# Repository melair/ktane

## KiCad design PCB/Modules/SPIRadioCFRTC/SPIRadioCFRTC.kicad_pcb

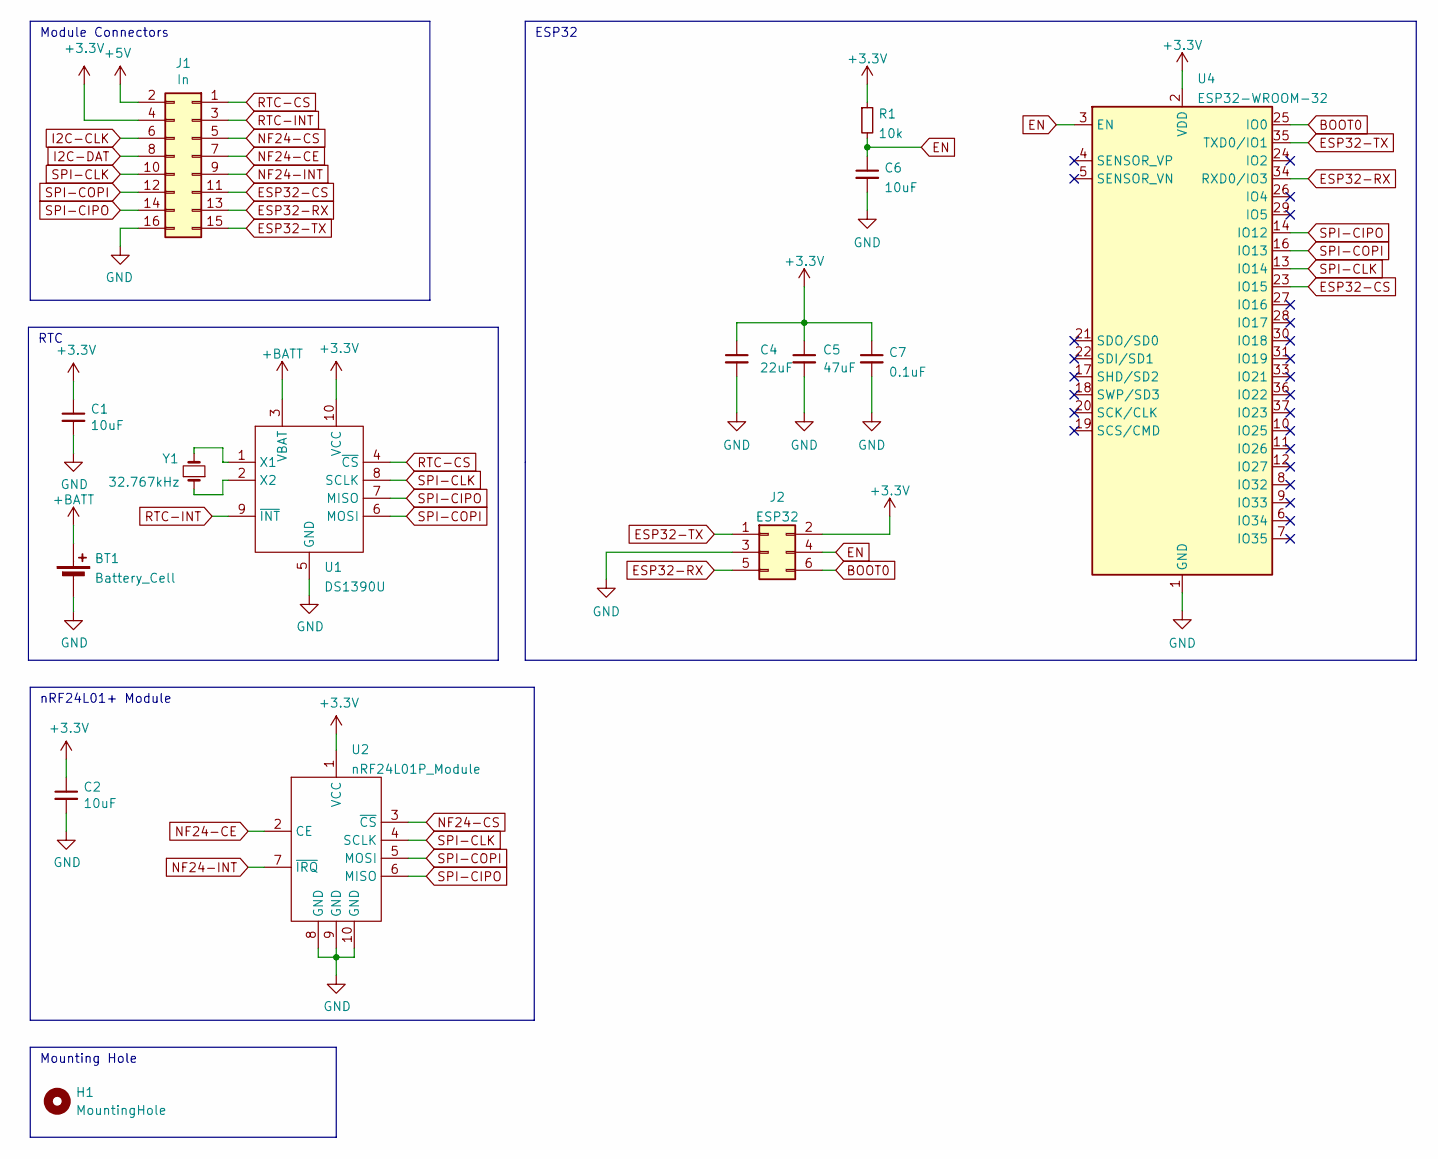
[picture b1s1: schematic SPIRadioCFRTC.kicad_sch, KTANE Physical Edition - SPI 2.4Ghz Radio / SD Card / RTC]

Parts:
BT1: Battery_Cell; CellHolder
C1, C2, C6: 10uF; C_0603_1608Metric
C4: 22uF; C_0603_1608Metric
C5: 47uF; C_0603_1608Metric
C7: 0.1uF; C_0603_1608Metric
H1: MountingHole; MountingHole_3.2mm_M3
J1: In; PinHeader_2x08_P2.54mm_Vertical-Centered
J2: ESP32; Tag-Connect_TC2030-IDC-NL_2x03_P1.27mm_Vertical
R1: 10k; R_0603_1608Metric
U1: DS1390U; MSOP-10_3x3mm_P0.5mm
U2: nRF24L01P_Module; NRF24L01P-Module
U4: ESP32-WROOM-32; ESP32-WROOM-32U
Y1: 32.767kHz; Crystal_SMD_3215-2Pin_3.2x1.5mm

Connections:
+3.3V: C1.1, C2.1, C4.1, C5.1, C7.1, J1.4, J2.2, R1.1, U1.10 (VCC), U2.1 (VCC), U4.2 (VDD)
+5V: J1.2
+BATT: BT1.1 (+), U1.3 (VBAT)
BOOT0: J2.6, U4.25 (IO0)
EN: C6.1, J2.4, R1.2, U4.3 (EN)
ESP32-CS: J1.11, U4.23 (IO15)
ESP32-RX: J1.13, J2.5, U4.34 (RXD0/IO3)
ESP32-TX: J1.15, J2.1, U4.35 (TXD0/IO1)
GND: BT1.2 (-), C1.2, C2.2, C4.2, C5.2, C6.2, C7.2, J1.16, J2.3, U1.5 (GND), U2.8 (GND), U2.9 (GND), U2.10 (GND), U4.1 (GND), U4.15 (GND), U4.38 (GND), U4.39 (GND)
I2C-CLK: J1.6
I2C-DAT: J1.8
NF24-CE: J1.7, U2.2 (CE)
NF24-CS: J1.5, U2.3 (~CS)
NF24-INT: J1.9, U2.7 (~IRQ)
unnamed: U1.1 (X1), Y1.2
unnamed: U1.2 (X2), Y1.1
RTC-CS: J1.1, U1.4 (~CS)
RTC-INT: J1.3, U1.9 (~INT)
SPI-CIPO: J1.14, U1.7 (MISO), U2.6 (MISO), U4.14 (IO12)
SPI-CLK: J1.10, U1.8 (SCLK), U2.4 (SCLK), U4.13 (IO14)
SPI-COPI: J1.12, U1.6 (MOSI), U2.5 (MOSI), U4.16 (IO13)

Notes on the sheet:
RTC
Module Connectors
nRF24L01+ Module
Mounting Hole
ESP32

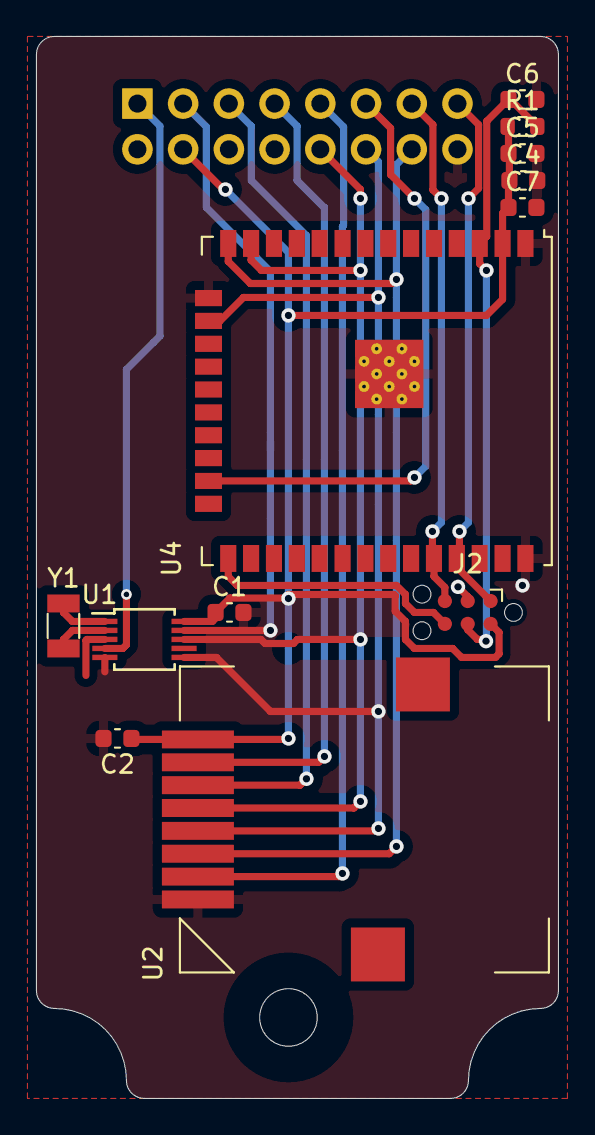
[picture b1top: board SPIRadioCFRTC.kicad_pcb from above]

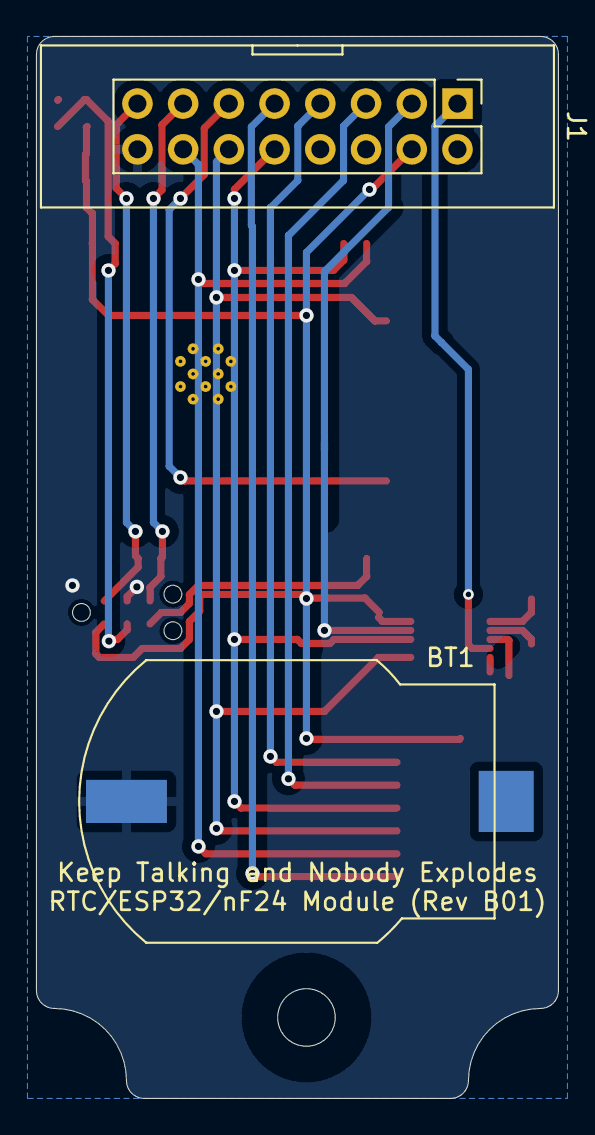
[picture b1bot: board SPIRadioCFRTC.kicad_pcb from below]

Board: 2 copper layers, 29.0 x 59.0 mm, 15 parts (2 on the bottom side), 18 nets.

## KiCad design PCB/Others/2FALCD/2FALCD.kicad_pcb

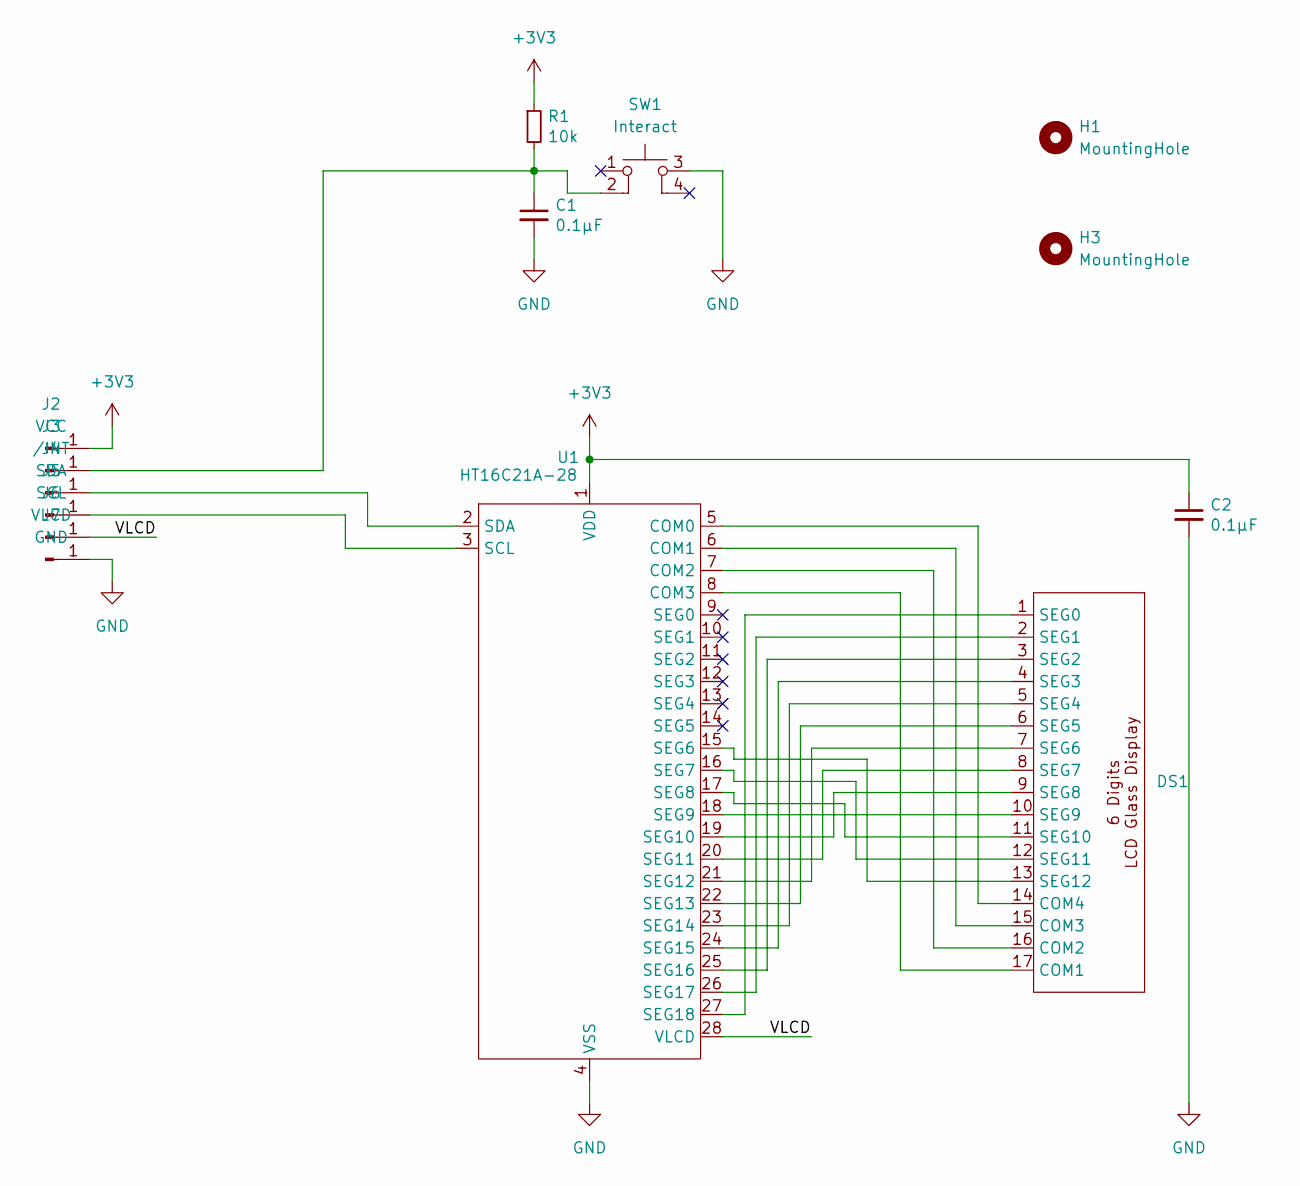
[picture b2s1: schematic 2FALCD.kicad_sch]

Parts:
C1, C2: 0.1μF; C_0603_1608Metric; DIGIKEY 1276-1005-1-ND
DS1: LCDGlass-6Digit
H1, H3: MountingHole; MountingHole_3.2mm_M3
J2: VCC; Pad4x2
J3: /INT; Pad4x2
J4: SDA; Pad4x2
J5: SCL; Pad4x2
J6: VLCD; Pad4x2
J7: GND; Pad4x2
R1: 10k; R_0603_1608Metric; DIGIKEY P10.0KHCT-ND
SW1: Interact; PTS526Sx15SMTR2xLFS; DIGIKEY CKN12220-1-ND
U1: HT16C21A-28; SOP-28_8.4x18.16mm_P1.27mm

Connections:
+3V3: C2.1, J2.1 (Pin_1_1), R1.1, U1.1 (VDD)
/VLCD: J6.1 (Pin_1_1), U1.28 (VLCD)
GND: C1.2, C2.2, J7.1 (Pin_1_1), SW1.3, U1.4 (VSS)
unnamed: DS1.17 (COM1), U1.8 (COM3)
unnamed: DS1.16 (COM2), U1.7 (COM2)
unnamed: DS1.15 (COM3), U1.6 (COM1)
unnamed: DS1.14 (COM4), U1.5 (COM0)
unnamed: DS1.1 (SEG0), U1.27 (SEG18)
unnamed: DS1.2 (SEG1), U1.26 (SEG17)
unnamed: DS1.3 (SEG2), U1.25 (SEG16)
unnamed: DS1.4 (SEG3), U1.24 (SEG15)
unnamed: DS1.5 (SEG4), U1.23 (SEG14)
unnamed: DS1.6 (SEG5), U1.22 (SEG13)
unnamed: DS1.7 (SEG6), U1.21 (SEG12)
unnamed: DS1.8 (SEG7), U1.20 (SEG11)
unnamed: DS1.9 (SEG8), U1.19 (SEG10)
unnamed: DS1.10 (SEG9), U1.18 (SEG9)
unnamed: DS1.11 (SEG10), U1.17 (SEG8)
unnamed: DS1.12 (SEG11), U1.16 (SEG7)
unnamed: DS1.13 (SEG12), U1.15 (SEG6)
unnamed: C1.1, J3.1 (Pin_1_1), R1.2, SW1.2
unnamed: J4.1 (Pin_1_1), U1.2 (SDA)
unnamed: J5.1 (Pin_1_1), U1.3 (SCL)

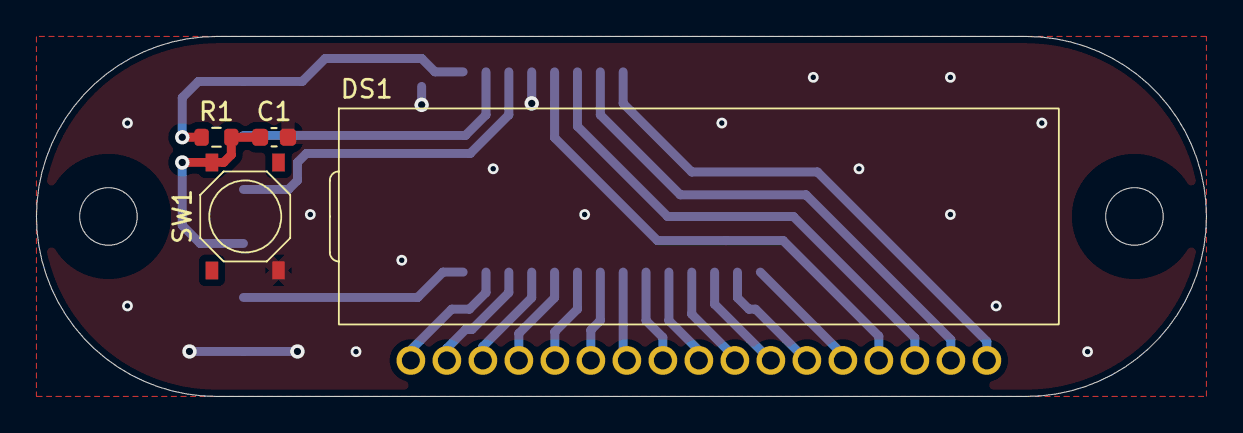
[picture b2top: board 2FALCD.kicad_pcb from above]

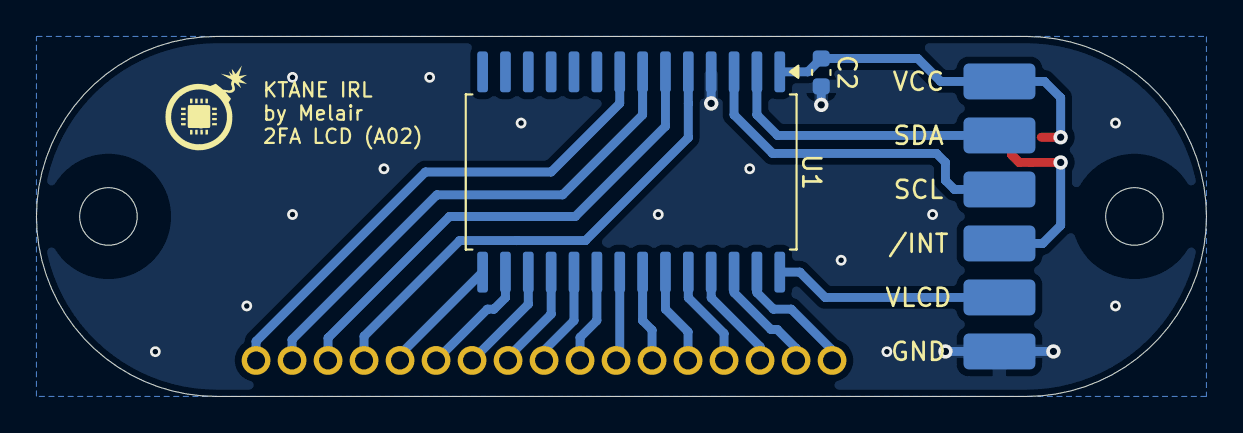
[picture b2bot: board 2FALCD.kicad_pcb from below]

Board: 2 copper layers, 65.0 x 20.0 mm, 14 parts (8 on the bottom side), 23 nets.

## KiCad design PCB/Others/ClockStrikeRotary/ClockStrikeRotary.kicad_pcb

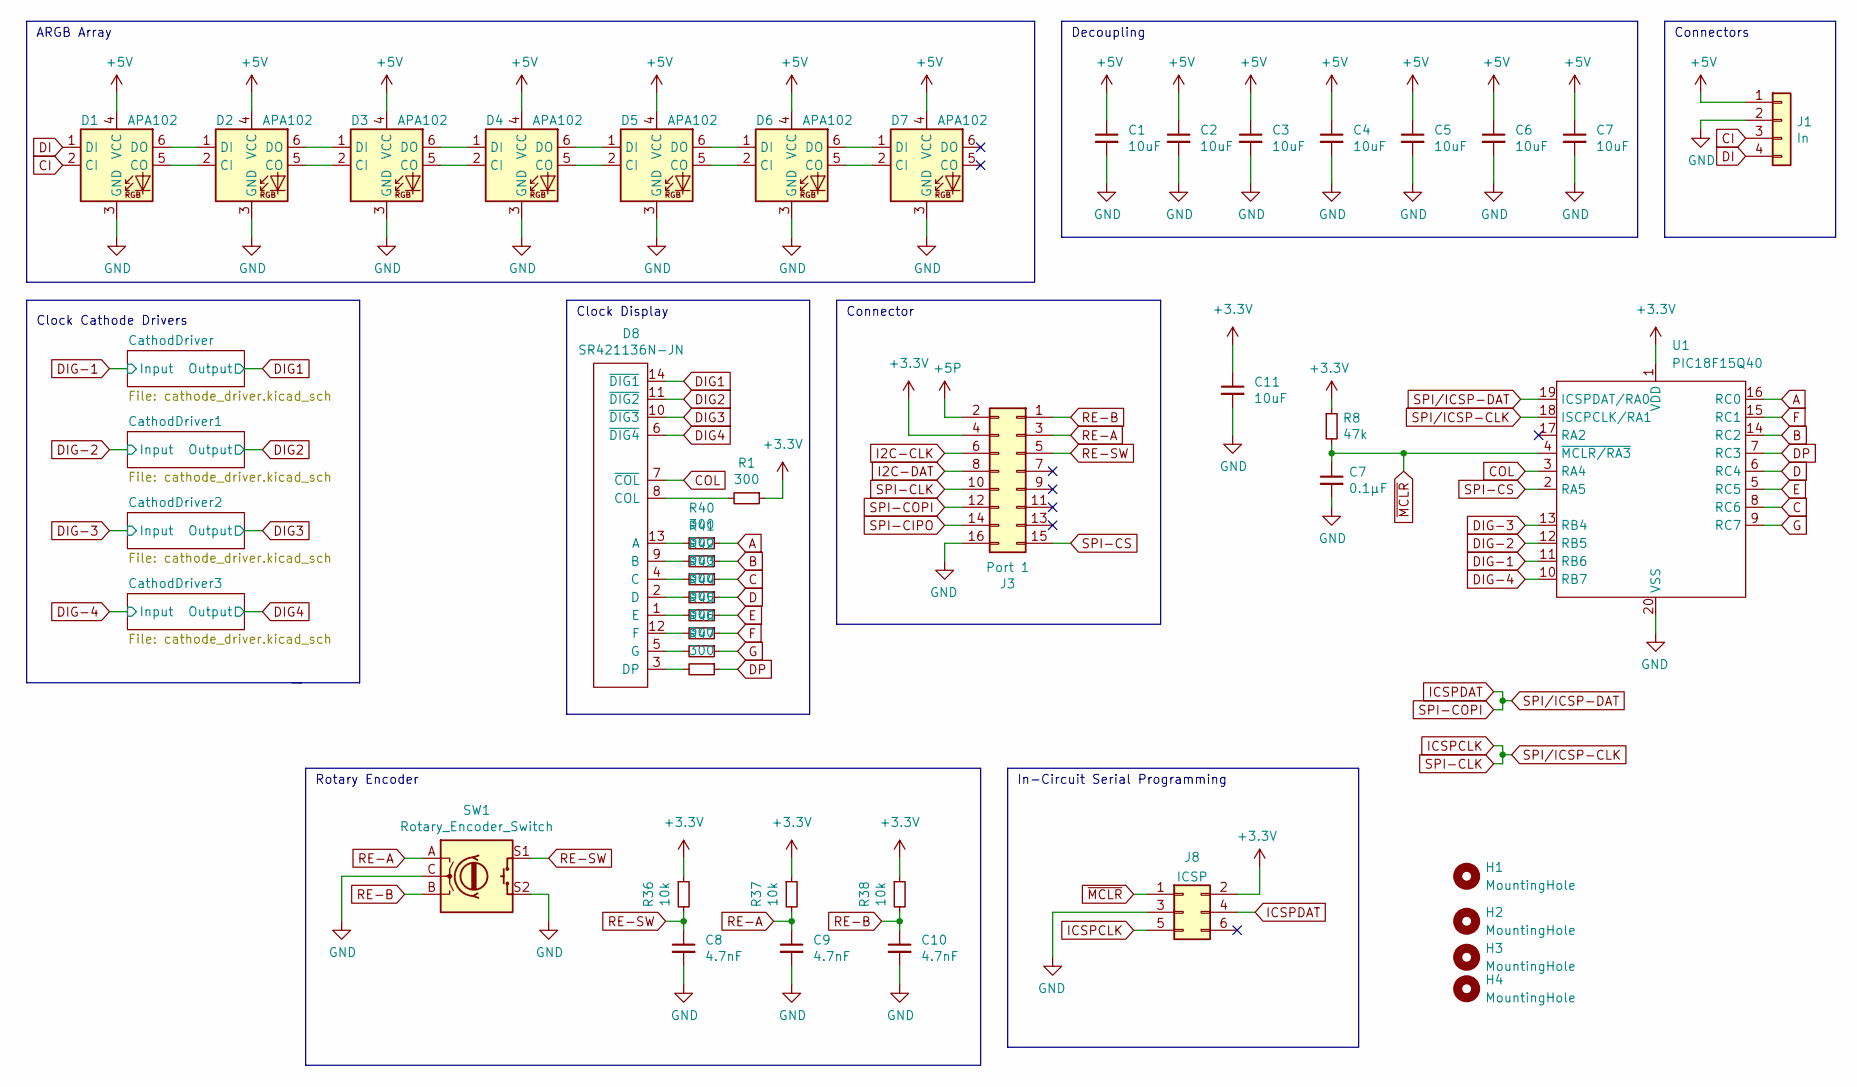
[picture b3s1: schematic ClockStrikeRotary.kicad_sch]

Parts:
C1, C2, C3, C4, C5, C6, C7, C11: 10uF; C_0603_1608Metric
C8, C9, C10: 4.7nF; C_0603_1608Metric
D1, D2, D3, D4, D5, D6, D7: APA102; LED_RGB_5050-6
D8: SR421136N-JN; ARK1136
H1, H2, H3, H4: MountingHole; MountingHole_3.2mm_M3
J1: In; JST_PH_B4B-PH-SM4-TB_1x04-1MP_P2.00mm_Vertical
J3: Port 1; PinHeader_2x08_P2.54mm_Vertical-Centered
J8: ICSP; Tag-Connect_TC2030-IDC-NL_2x03_P1.27mm_Vertical
R1, R40, R41, R42, R43, R44, R45, R46, R47: 300; R_0603_1608Metric
R8: 47k; R_0603_1608Metric
R36, R37, R38: 10k; R_0603_1608Metric
SW1: Rotary_Encoder_Switch; RotaryEncoder_Alps_EC11E-Switch_Vertical_H20mm
U1: PIC18F15Q40; SSOP-20_5.3x7.2mm_P0.65mm

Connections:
+3.3V: C11.1, J3.4, R1.1, R36.1, R37.1, R38.1, U1.1 (VDD); also elsewhere on the board
+5P: J3.2
A: R40.1, U1.16 (RC0)
B: R41.1, U1.14 (RC2)
C: R42.1, U1.8 (RC6)
CI: D1.2 (CI), J1.3
COL: D8.7 (~COL), U1.3 (RA4)
D: R43.1, U1.6 (RC4)
DI: D1.1 (DI), J1.4
DIG1: D8.14 (~DIG1); also elsewhere on the board
DIG2: D8.11 (~DIG2); also elsewhere on the board
DIG3: D8.10 (~DIG3); also elsewhere on the board
DIG4: D8.6 (~DIG4); also elsewhere on the board
DIG-1: U1.11 (RB6); also elsewhere on the board
DIG-2: U1.12 (RB5); also elsewhere on the board
DIG-3: U1.13 (RB4); also elsewhere on the board
DIG-4: U1.10 (RB7); also elsewhere on the board
DP: R47.1, U1.7 (RC3)
E: R44.1, U1.5 (RC5)
F: R45.1, U1.15 (RC1)
G: R46.1, U1.9 (RC7)
GND: C1.2, C2.2, C3.2, C4.2, C5.2, C6.2, C7.2, C8.2, C9.2, C10.2, C11.2, D1.3 (GND), D2.3 (GND), D3.3 (GND), D4.3 (GND), D5.3 (GND), D6.3 (GND), D7.3 (GND), J1.2, J3.16, SW1.C, SW1.S2, U1.20 (VSS); also elsewhere on the board
I2C-CLK: J3.6
I2C-DAT: J3.8
ICSPCLK: J3.10, U1.18 (ISCPCLK/RA1); also elsewhere on the board
ICSPDAT: J3.12, U1.19 (ICSPDAT/RA0); also elsewhere on the board
unnamed: D1.5 (CO), D2.2 (CI)
unnamed: D1.6 (DO), D2.1 (DI)
unnamed: D2.5 (CO), D3.2 (CI)
unnamed: D2.6 (DO), D3.1 (DI)
unnamed: D3.5 (CO), D4.2 (CI)
unnamed: D3.6 (DO), D4.1 (DI)
unnamed: D4.5 (CO), D5.2 (CI)
unnamed: D4.6 (DO), D5.1 (DI)
unnamed: D5.5 (CO), D6.2 (CI)
unnamed: D5.6 (DO), D6.1 (DI)
unnamed: D6.5 (CO), D7.2 (CI)
unnamed: D6.6 (DO), D7.1 (DI)
unnamed: D8.13 (A), R40.2
unnamed: D8.9 (B), R41.2
unnamed: D8.4 (C), R42.2
unnamed: D8.8 (COL), R1.2
unnamed: D8.2 (D), R43.2
unnamed: D8.3 (DP), R47.2
unnamed: D8.1 (E), R44.2
unnamed: D8.12 (F), R45.2
unnamed: D8.5 (G), R46.2
RE-A: C9.1, J3.3, R37.2, SW1.A
RE-B: C10.1, J3.1, R38.2, SW1.B
RE-SW: C8.1, J3.5, R36.2, SW1.S1
SPI-CIPO: J3.14
SPI-CS: J3.15, U1.2 (RA5)

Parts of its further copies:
J4: ICSP; Tag-Connect_TC2030-IDC-NL_2x03_P1.27mm_Vertical
R39: 47k; R_0603_1608Metric

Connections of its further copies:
+3.3V: J4.2, R39.1; also elsewhere on the board
GND: J4.3; also elsewhere on the board
ICSPCLK: J4.5; also elsewhere on the board
ICSPDAT: J4.4; also elsewhere on the board

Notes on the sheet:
Clock Cathode Drivers
In-Circuit Serial Programming
Rotary Encoder
Connectors
Connector
Decoupling
ARGB Array
Clock Display

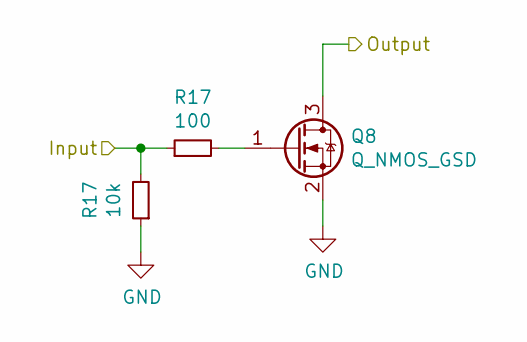
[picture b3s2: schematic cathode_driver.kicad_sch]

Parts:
Q8: Q_NMOS_GSD; SOT-23
R17: 100; R_0603_1608Metric

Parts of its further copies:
Q9, Q10, Q11, Q12: Q_NMOS_GSD; SOT-23
R18, R29, R31, R33: 100; R_0603_1608Metric

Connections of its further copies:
DIG1: Q9.3 (D); also elsewhere on the board
DIG2: Q10.3 (D); also elsewhere on the board
DIG3: Q11.3 (D); also elsewhere on the board
DIG4: Q12.3 (D); also elsewhere on the board
DIG-1: R18.1; also elsewhere on the board
DIG-2: R29.1; also elsewhere on the board
DIG-3: R31.1; also elsewhere on the board
DIG-4: R33.1; also elsewhere on the board
GND: Q9.2 (S), Q10.2 (S), Q11.2 (S), Q12.2 (S); also elsewhere on the board
unnamed: Q9.1 (G), R18.2
unnamed: Q10.1 (G), R29.2
unnamed: Q11.1 (G), R31.2
unnamed: Q12.1 (G), R33.2

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
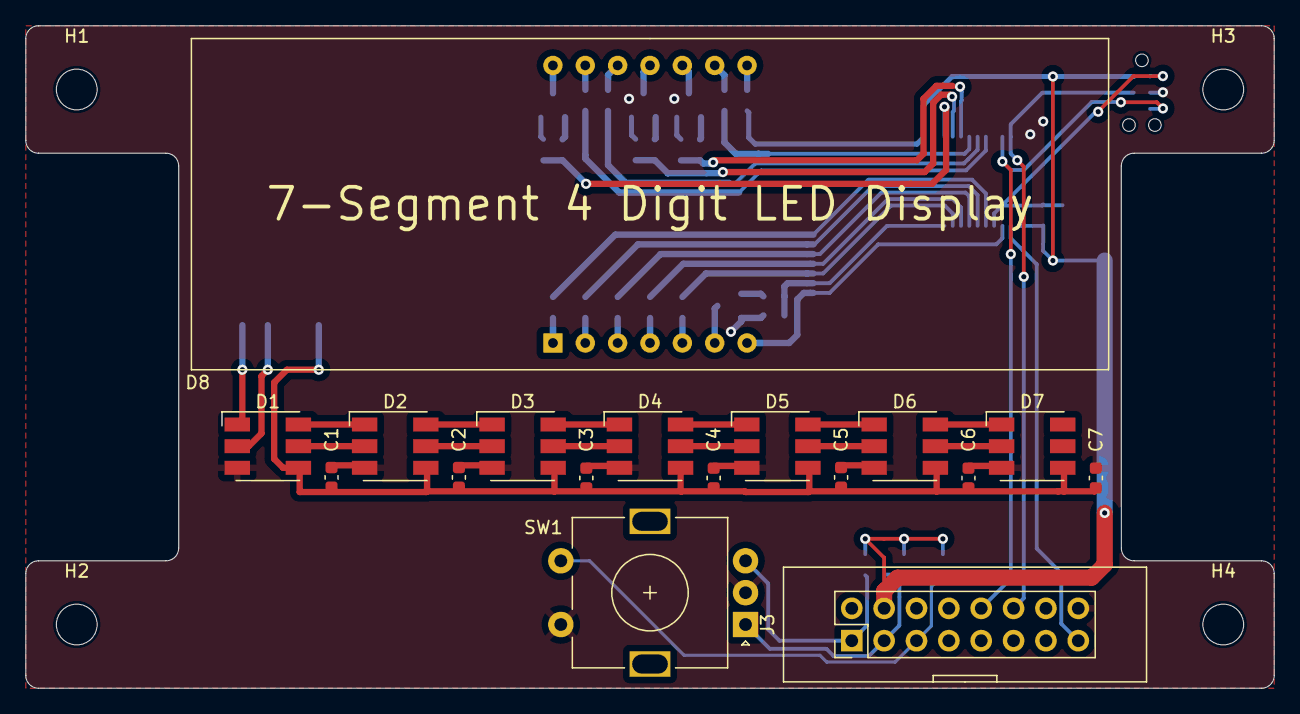
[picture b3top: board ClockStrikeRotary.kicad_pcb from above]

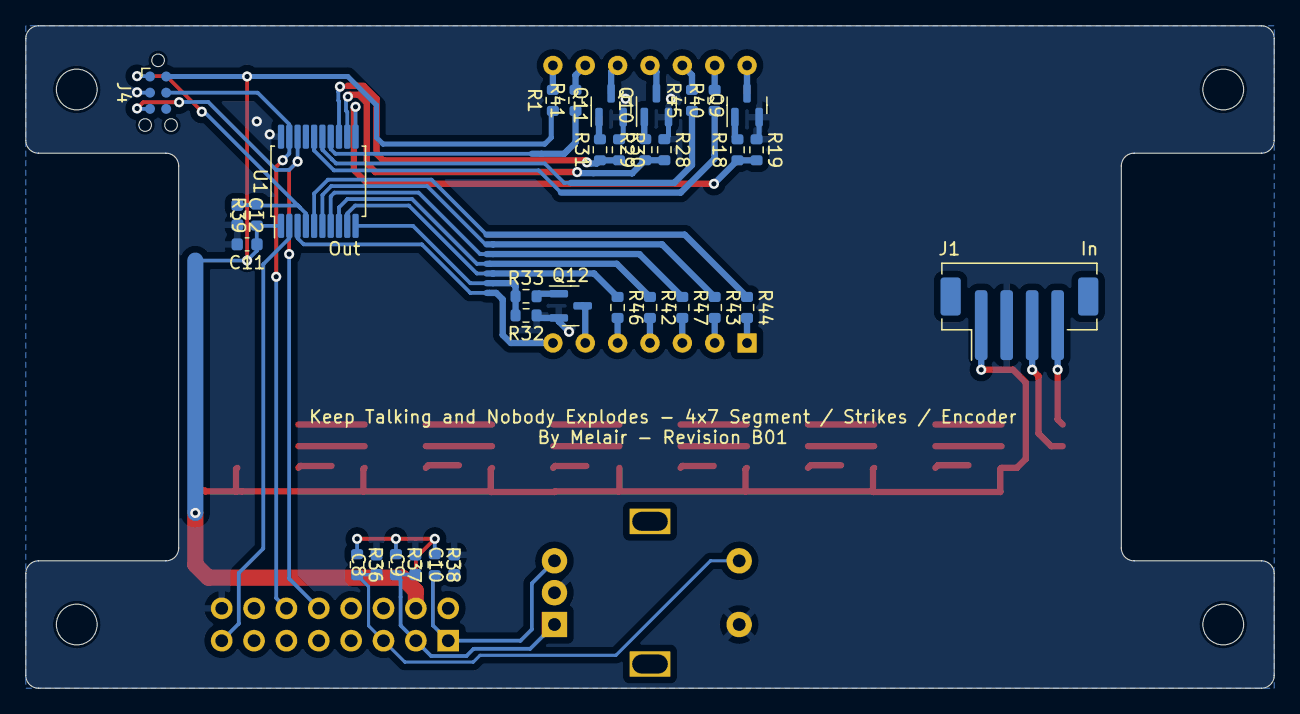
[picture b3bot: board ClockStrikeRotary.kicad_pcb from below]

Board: 2 copper layers, 98.0 x 52.0 mm, 54 parts (33 on the bottom side), 54 nets.

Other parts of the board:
C12: 0.1μF; C_0603_1608Metric
R19, R28, R30, R32: 10k; R_0603_1608Metric

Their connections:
DIG-1: R19.2; also elsewhere on the board
DIG-2: R28.2; also elsewhere on the board
DIG-3: R30.2; also elsewhere on the board
DIG-4: R32.2; also elsewhere on the board
GND: C12.2, R19.1, R28.1, R30.1, R32.1; also elsewhere on the board

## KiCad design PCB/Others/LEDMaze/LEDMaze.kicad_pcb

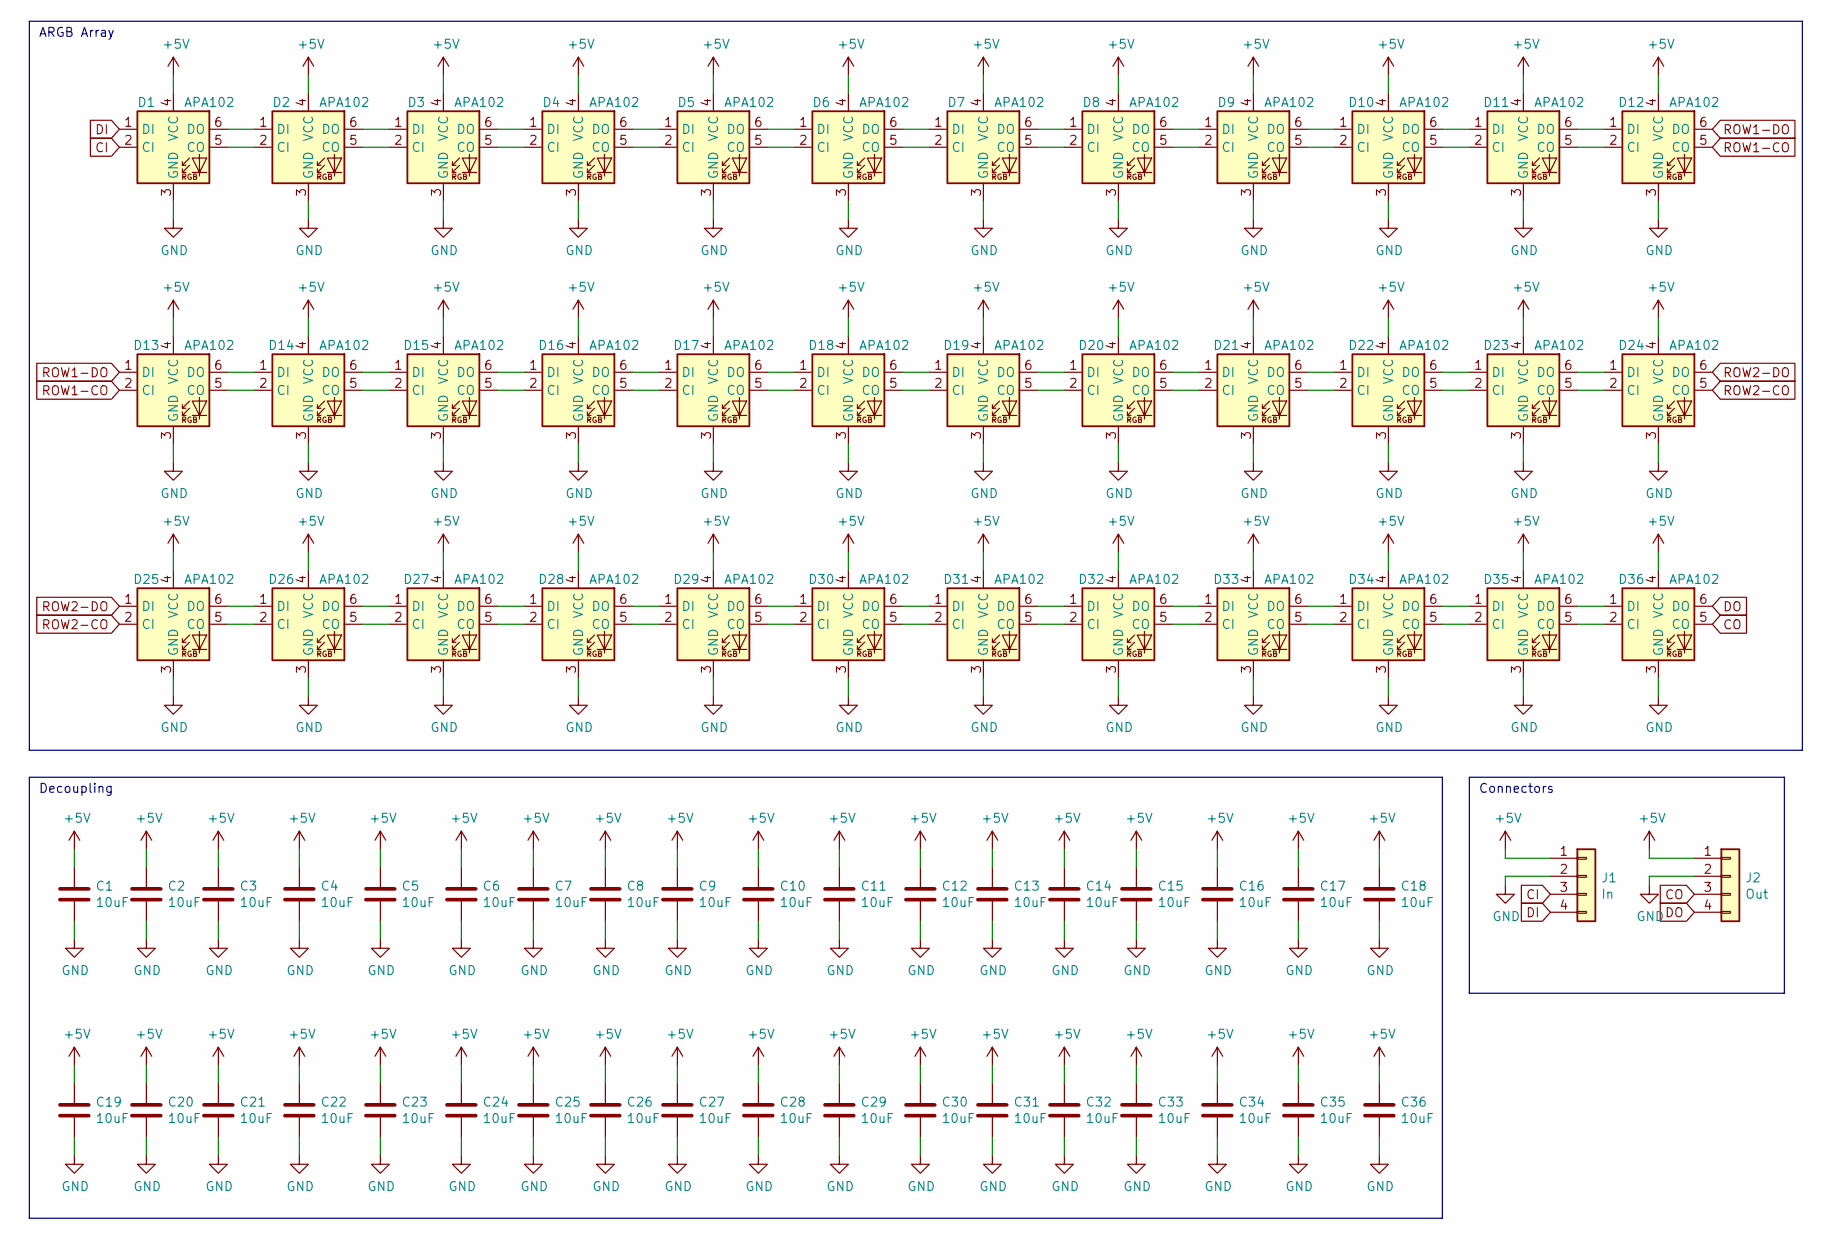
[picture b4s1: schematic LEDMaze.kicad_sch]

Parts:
C1, C2, C3, C4, C5, C6, C7, C8, C9, C10, C11, C12, C13, C14, C15, C16, C17, C18, C19, C20, C21, C22, C23, C24, C25, C26, C27, C28, C29, C30, C31, C32, C33, C34, C35, C36: 10uF; C_0805_2012Metric
D1, D2, D3, D4, D5, D6, D7, D8, D9, D10, D11, D12, D13, D14, D15, D16, D17, D18, D19, D20, D21, D22, D23, D24, D25, D26, D27, D28, D29, D30, D31, D32, D33, D34, D35, D36: APA102; LED_RGB_5050-6
J1: In; JST_PH_B4B-PH-SM4-TB_1x04-1MP_P2.00mm_Vertical
J2: Out; JST_PH_B4B-PH-SM4-TB_1x04-1MP_P2.00mm_Vertical

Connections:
+5V: C1.1, C2.1, C3.1, C4.1, C5.1, C6.1, C7.1, C8.1, C9.1, C10.1, C11.1, C12.1, C13.1, C14.1, C15.1, C16.1, C17.1, C18.1, C19.1, C20.1, C21.1, C22.1, C23.1, C24.1, C25.1, C26.1, C27.1, C28.1, C29.1, C30.1, C31.1, C32.1, C33.1, C34.1, C35.1, C36.1, D1.4 (VCC), D2.4 (VCC), D3.4 (VCC), D4.4 (VCC), D5.4 (VCC), D6.4 (VCC), D7.4 (VCC), D8.4 (VCC), D9.4 (VCC), D10.4 (VCC), D11.4 (VCC), D12.4 (VCC), D13.4 (VCC), D14.4 (VCC), D15.4 (VCC), D16.4 (VCC), D17.4 (VCC), D18.4 (VCC), D19.4 (VCC), D20.4 (VCC), D21.4 (VCC), D22.4 (VCC), D23.4 (VCC), D24.4 (VCC), D25.4 (VCC), D26.4 (VCC), D27.4 (VCC), D28.4 (VCC), D29.4 (VCC), D30.4 (VCC), D31.4 (VCC), D32.4 (VCC), D33.4 (VCC), D34.4 (VCC), D35.4 (VCC), D36.4 (VCC), J1.1, J2.1
CI: D1.2 (CI), J1.3
CO: D36.5 (CO), J2.3
DI: D1.1 (DI), J1.4
DO: D36.6 (DO), J2.4
GND: C1.2, C2.2, C3.2, C4.2, C5.2, C6.2, C7.2, C8.2, C9.2, C10.2, C11.2, C12.2, C13.2, C14.2, C15.2, C16.2, C17.2, C18.2, C19.2, C20.2, C21.2, C22.2, C23.2, C24.2, C25.2, C26.2, C27.2, C28.2, C29.2, C30.2, C31.2, C32.2, C33.2, C34.2, C35.2, C36.2, D1.3 (GND), D2.3 (GND), D3.3 (GND), D4.3 (GND), D5.3 (GND), D6.3 (GND), D7.3 (GND), D8.3 (GND), D9.3 (GND), D10.3 (GND), D11.3 (GND), D12.3 (GND), D13.3 (GND), D14.3 (GND), D15.3 (GND), D16.3 (GND), D17.3 (GND), D18.3 (GND), D19.3 (GND), D20.3 (GND), D21.3 (GND), D22.3 (GND), D23.3 (GND), D24.3 (GND), D25.3 (GND), D26.3 (GND), D27.3 (GND), D28.3 (GND), D29.3 (GND), D30.3 (GND), D31.3 (GND), D32.3 (GND), D33.3 (GND), D34.3 (GND), D35.3 (GND), D36.3 (GND), J1.2, J2.2
unnamed: D1.5 (CO), D2.2 (CI)
unnamed: D1.6 (DO), D2.1 (DI)
unnamed: D2.5 (CO), D3.2 (CI)
unnamed: D2.6 (DO), D3.1 (DI)
unnamed: D3.5 (CO), D4.2 (CI)
unnamed: D3.6 (DO), D4.1 (DI)
unnamed: D4.5 (CO), D5.2 (CI)
unnamed: D4.6 (DO), D5.1 (DI)
unnamed: D5.5 (CO), D6.2 (CI)
unnamed: D5.6 (DO), D6.1 (DI)
unnamed: D6.5 (CO), D7.2 (CI)
unnamed: D6.6 (DO), D7.1 (DI)
unnamed: D7.5 (CO), D8.2 (CI)
unnamed: D7.6 (DO), D8.1 (DI)
unnamed: D8.5 (CO), D9.2 (CI)
unnamed: D8.6 (DO), D9.1 (DI)
unnamed: D9.6 (DO), D10.1 (DI)
unnamed: D9.5 (CO), D10.2 (CI)
unnamed: D10.5 (CO), D11.2 (CI)
unnamed: D10.6 (DO), D11.1 (DI)
unnamed: D11.5 (CO), D12.2 (CI)
unnamed: D11.6 (DO), D12.1 (DI)
unnamed: D13.5 (CO), D14.2 (CI)
unnamed: D13.6 (DO), D14.1 (DI)
unnamed: D14.5 (CO), D15.2 (CI)
unnamed: D14.6 (DO), D15.1 (DI)
unnamed: D15.5 (CO), D16.2 (CI)
unnamed: D15.6 (DO), D16.1 (DI)
unnamed: D16.5 (CO), D17.2 (CI)
unnamed: D16.6 (DO), D17.1 (DI)
unnamed: D17.5 (CO), D18.2 (CI)
unnamed: D17.6 (DO), D18.1 (DI)
unnamed: D18.5 (CO), D19.2 (CI)
unnamed: D18.6 (DO), D19.1 (DI)
unnamed: D19.5 (CO), D20.2 (CI)
unnamed: D19.6 (DO), D20.1 (DI)
unnamed: D20.5 (CO), D21.2 (CI)
unnamed: D20.6 (DO), D21.1 (DI)
unnamed: D21.5 (CO), D22.2 (CI)
unnamed: D21.6 (DO), D22.1 (DI)
unnamed: D22.5 (CO), D23.2 (CI)
unnamed: D22.6 (DO), D23.1 (DI)
unnamed: D23.5 (CO), D24.2 (CI)
unnamed: D23.6 (DO), D24.1 (DI)
unnamed: D25.5 (CO), D26.2 (CI)
unnamed: D25.6 (DO), D26.1 (DI)
unnamed: D26.5 (CO), D27.2 (CI)
unnamed: D26.6 (DO), D27.1 (DI)
unnamed: D27.5 (CO), D28.2 (CI)
unnamed: D27.6 (DO), D28.1 (DI)
unnamed: D28.5 (CO), D29.2 (CI)
unnamed: D28.6 (DO), D29.1 (DI)
unnamed: D29.5 (CO), D30.2 (CI)
unnamed: D29.6 (DO), D30.1 (DI)
unnamed: D30.5 (CO), D31.2 (CI)
unnamed: D30.6 (DO), D31.1 (DI)
unnamed: D31.5 (CO), D32.2 (CI)
unnamed: D31.6 (DO), D32.1 (DI)
unnamed: D32.5 (CO), D33.2 (CI)
unnamed: D32.6 (DO), D33.1 (DI)
unnamed: D33.5 (CO), D34.2 (CI)
unnamed: D33.6 (DO), D34.1 (DI)
unnamed: D34.5 (CO), D35.2 (CI)
unnamed: D34.6 (DO), D35.1 (DI)
unnamed: D35.5 (CO), D36.2 (CI)
unnamed: D35.6 (DO), D36.1 (DI)
ROW1-CO: D12.5 (CO), D13.2 (CI)
ROW1-DO: D12.6 (DO), D13.1 (DI)
ROW2-CO: D24.5 (CO), D25.2 (CI)
ROW2-DO: D24.6 (DO), D25.1 (DI)

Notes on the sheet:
Connectors
ARGB Array
Decoupling

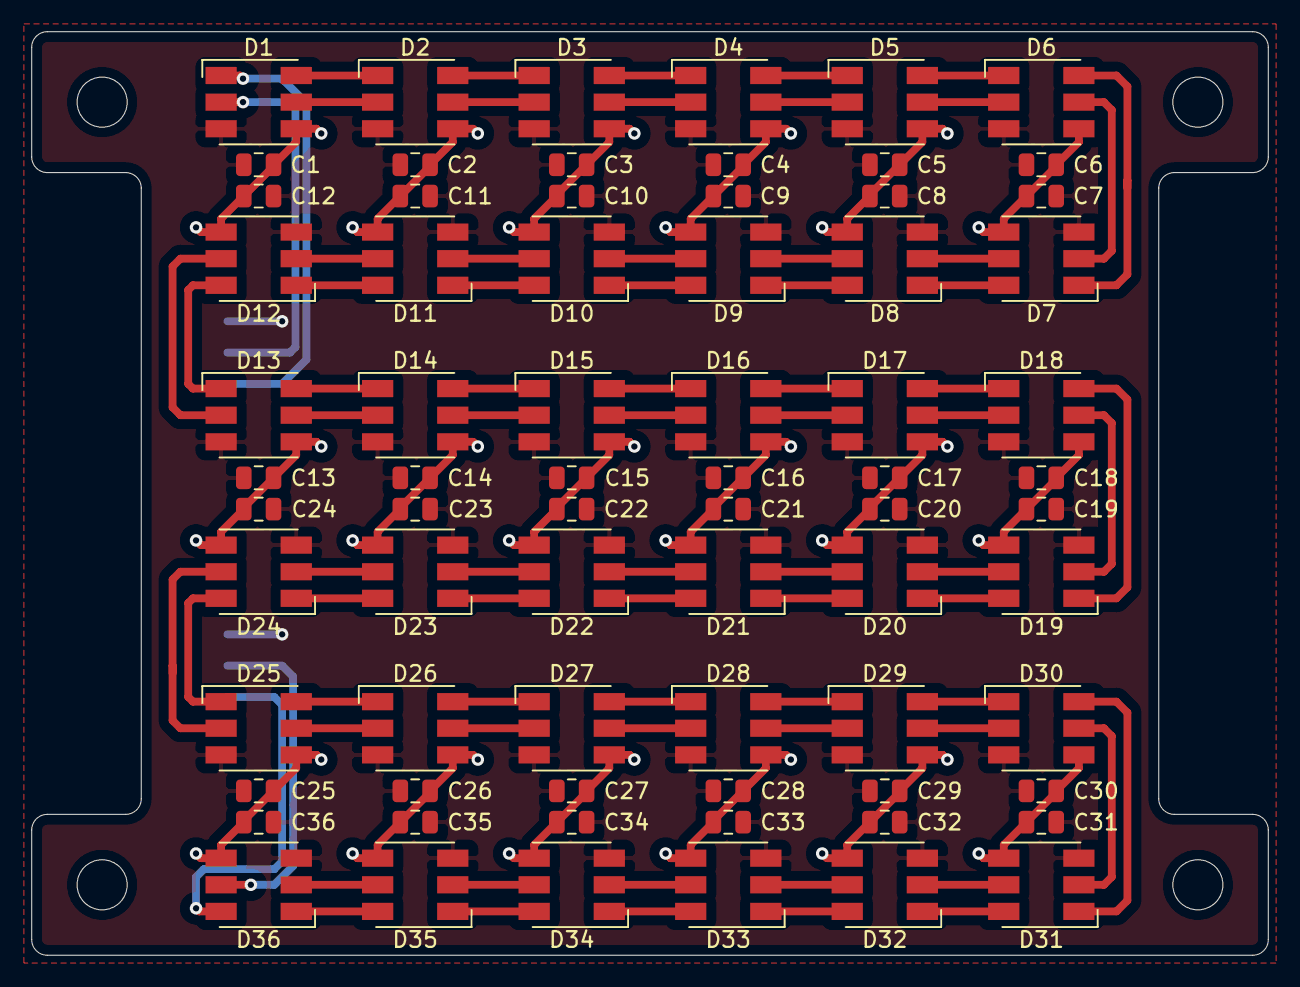
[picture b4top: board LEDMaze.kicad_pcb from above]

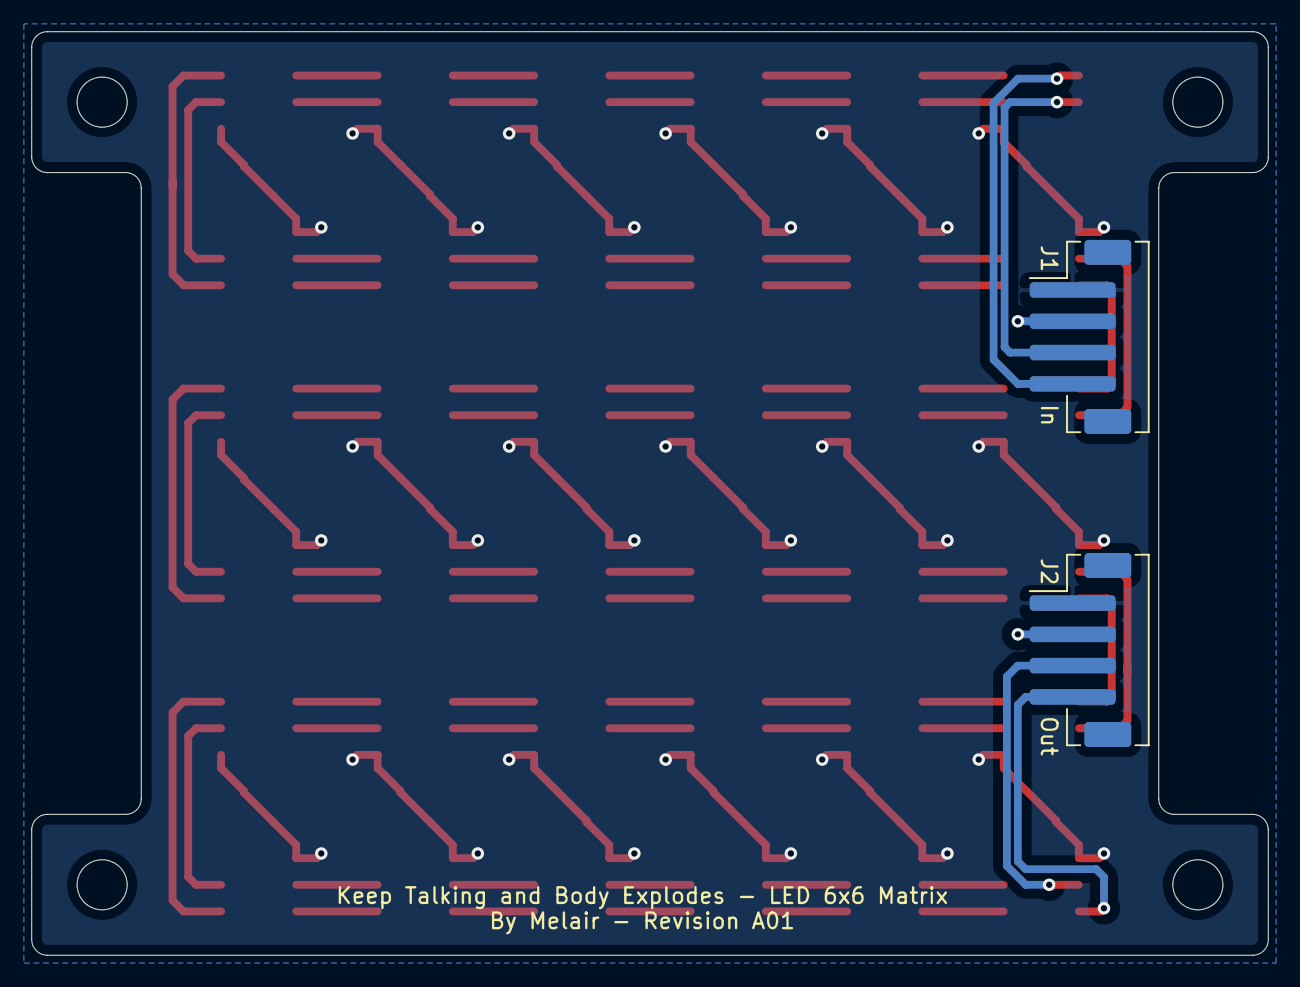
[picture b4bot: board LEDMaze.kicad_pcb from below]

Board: 2 copper layers, 79.0 x 59.0 mm, 74 parts (2 on the bottom side), 76 nets.
